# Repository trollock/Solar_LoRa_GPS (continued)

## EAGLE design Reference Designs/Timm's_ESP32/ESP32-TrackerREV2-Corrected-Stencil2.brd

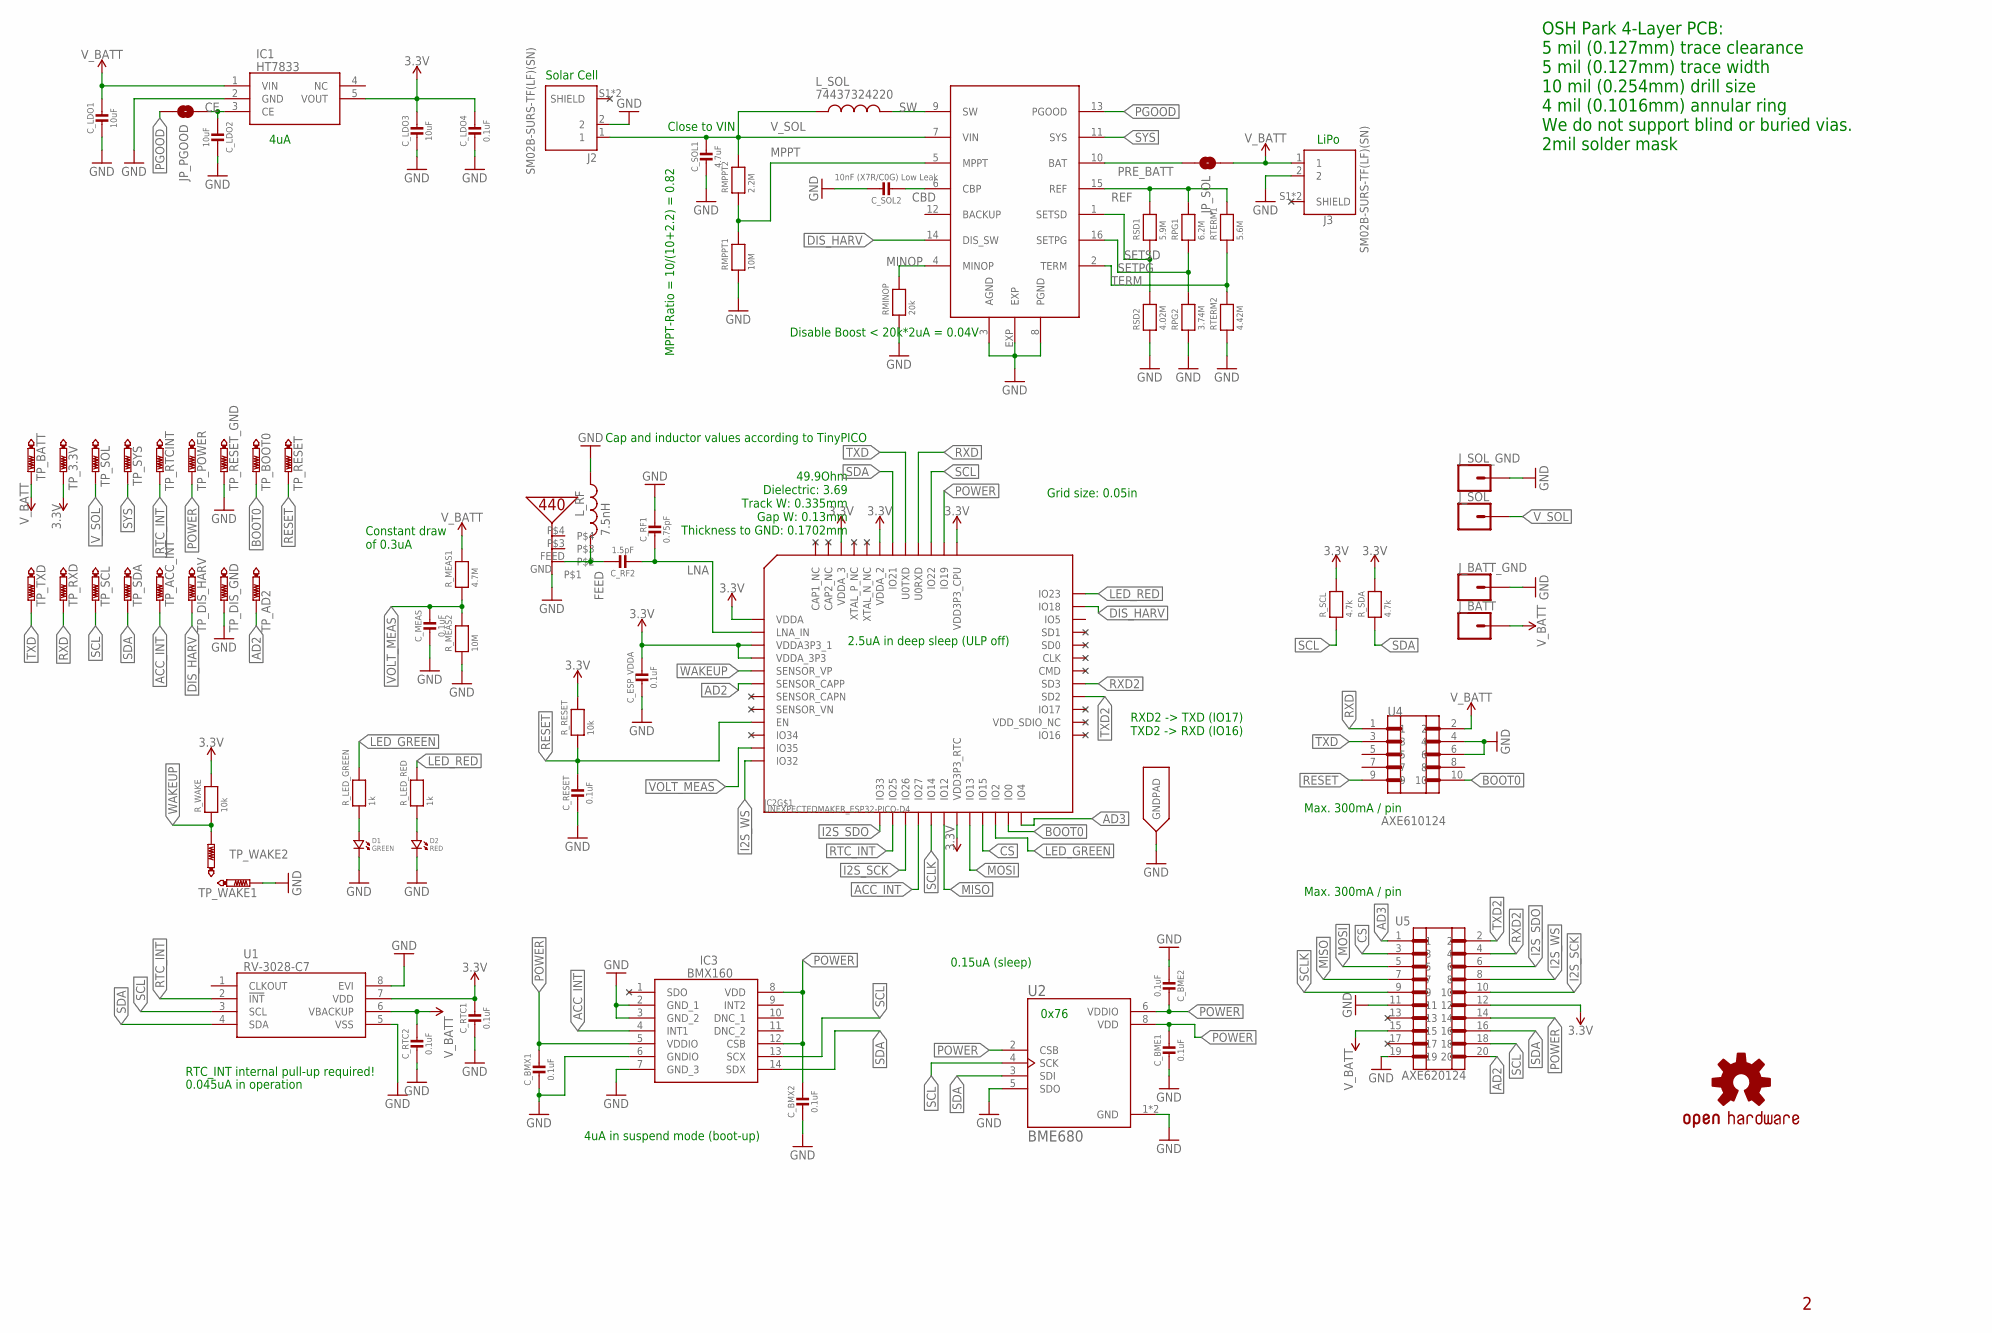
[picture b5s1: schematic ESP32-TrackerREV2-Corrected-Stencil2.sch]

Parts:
C_BME1, C_BME2: 0.1uF; MICROBUILDER__0402MP
C_BMX1, C_BMX2: 0.1uF; MICROBUILDER__0402MP
C_ESP_VDDA: 0.1uF; MICROBUILDER__0402MP
C_LDO1, C_LDO2, C_LDO3: 10uF; MICROBUILDER__0402MP
C_LDO4: 0.1uF; MICROBUILDER__0402MP
C_MEAS: 0.1uF; MICROBUILDER__0402MP
C_RESET: 0.1uF; MICROBUILDER__0402MP
C_RF1: 0.75pF; MICROBUILDER__0402MP
C_RF2: 1.5pF; MICROBUILDER__0402MP
C_RTC1, C_RTC2: 0.1uF; MICROBUILDER__0402MP
C_SOL1: 4.7uF; MICROBUILDER__0402MP
C_SOL2: 10nF (X7R/C0G) Low Leak; MICROBUILDER__0402MP
D1: GREEN; CMONR_STANDARDPARTS_0402.LED
D2: RED; CMONR_STANDARDPARTS_0402.LED
IC1: HT7833; SOT95P280X80-5N
IC2: UNEXPECTEDMAKER_ESP32-PICO-D4; UNEXPECTEDMAKER_PICO-D4-QFN48
IC3: BMX160; PQFN50P300X250X88-14N
J2, J3: SM02B-SURS-TF(LF)(SN); JST_SM02B-SURS-TF(LF)(SN)
JP_PGOOD: JUMPER-SMT_2_NO_NO-SILK; SMT-JUMPER_2_NO_NO-SILK
JP_SOL: JUMPER-SMT_2_NO_NO-SILK; SMT-JUMPER_2_NO_NO-SILK
J_BATT: CONN_01PTH_NO_SILK_SMALL; 1X01_SMALL
J_BATT_GND: CONN_01PTH_NO_SILK_SMALL; 1X01_SMALL
J_SOL: CONN_01PTH_NO_SILK_SMALL; 1X01_SMALL
J_SOL_GND: CONN_01PTH_NO_SILK_SMALL; 1X01_SMALL
LOGO1: OSHW-LOGOS; OSHW-LOGO-S
L_RF: 7.5nH; NORDIC_NRF_RESC0402_N
L_SOL: 74437324220; IND_74437324220
RMINOP: 20k; MICROBUILDER__0402MP
RMPPT1: 10M; MICROBUILDER__0402MP
RMPPT2: 2.2M; MICROBUILDER__0402MP
RPG1: 6.2M; MICROBUILDER__0402MP
RPG2: 3.74M; MICROBUILDER__0402MP
RSD1: 5.9M; MICROBUILDER__0402MP
RSD2: 4.02M; MICROBUILDER__0402MP
RTERM1: 5.6M; MICROBUILDER__0402MP
RTERM2: 4.42M; MICROBUILDER__0402MP
R_LED_GREEN: 1k; MICROBUILDER__0402MP
R_LED_RED: 1k; MICROBUILDER__0402MP
R_MEAS1: 4.7M; MICROBUILDER__0402MP
R_MEAS2: 10M; MICROBUILDER__0402MP
R_RESET: 10k; MICROBUILDER__0402MP
R_SCL: 4.7k; MICROBUILDER__0402MP
R_SDA: 4.7k; MICROBUILDER__0402MP
R_WAKE: 10k; MICROBUILDER__0402MP
TP_3.3V: PTR1TP06SQ; TP06SQ
TP_ACC_INT: PTR1TP06SQ; TP06SQ
TP_AD2: PTR1TP06SQ; TP06SQ
TP_BATT: PTR1TP06SQ; TP06SQ
TP_BOOT0: PTR1TP06SQ; TP06SQ
TP_DIS_GND: PTR1TP06SQ; TP06SQ
TP_DIS_HARV: PTR1TP06SQ; TP06SQ
TP_POWER: PTR1TP06SQ; TP06SQ
TP_RESET: PTR1TP06SQ; TP06SQ
TP_RESET_GND: PTR1TP06SQ; TP06SQ
TP_RTCINT: PTR1TP06SQ; TP06SQ
TP_RXD: PTR1TP06SQ; TP06SQ
TP_SCL: PTR1TP06SQ; TP06SQ
TP_SDA: PTR1TP06SQ; TP06SQ
TP_SOL: PTR1TP06SQ; TP06SQ
TP_SYS: PTR1TP06SQ; TP06SQ
TP_TXD: PTR1TP06SQ; TP06SQ
TP_WAKE1, TP_WAKE2: PTR1TP06SQ; TP06SQ
U1: RV-3028-C7; RV3028C7
U2: BME680; PSON80P300X300X100-8N
U3: UNEXPECTEDMAKER_PRO-OB-440
U4: AXE610124
U5: AXE620124
U6: ADP5090_LFCSP-16-3X3_ADP5090; ADP5090_LFCSP-16-3X3_LFCSP-16-3X3

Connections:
3.3V: C_ESP_VDDA.1, C_LDO3.1, C_LDO4.1, C_RTC1.1, IC1.5 (VOUT), IC2.1 (VDDA), IC2.3 (VDDA3P3_1), IC2.4 (VDDA_3P3), IC2.19 (VDD3P3_RTC), IC2.37 (VDD3P3_CPU), IC2.43 (VDDA_2), IC2.46 (VDDA_3), R_RESET.2, R_SCL.2, R_SDA.2, R_WAKE.2, TP_3.3V.TP, U1.7 (VDD), U5.12
ACC_INT: IC2.16 (IO27), IC3.4 (INT1), TP_ACC_INT.TP
AD2: IC2.6 (SENSOR_CAPP), TP_AD2.TP, U5.20
AD3: IC2.24 (IO4), U5.1
BOOT0: IC2.23 (IO0), TP_BOOT0.TP, U4.10
CBD: C_SOL2.2, U6.6 (CBP)
CE: C_LDO2.2, IC1.3 (CE), JP_PGOOD.2
CS: IC2.21 (IO15), U5.3
DIS_HARV: IC2.35 (IO18), TP_DIS_HARV.TP, U6.14 (DIS_SW)
FEED: C_RF2.1, L_RF.2, U3.FEED
GND: C_BME1.2, C_BME2.2, C_BMX1.2, C_BMX2.2, C_ESP_VDDA.2, C_LDO1.2, C_LDO2.1, C_LDO3.2, C_LDO4.2, C_MEAS.2, C_RESET.2, C_RF1.1, C_RTC1.2, C_RTC2.2, C_SOL1.2, C_SOL2.1, D1.P$2 (2), D2.P$2 (2), IC1.2 (GND), IC2.EXP (GNDPAD), IC3.2 (GND_1), IC3.3 (GND_2), IC3.6 (GNDIO), IC3.7 (GND_3), J2.2, J3.2, J_BATT_GND.P$1, J_SOL_GND.P$1, L_RF.1, RMINOP.1, RMPPT1.1, RPG2.1, RSD2.1, RTERM2.1, R_MEAS2.1, TP_DIS_GND.TP, TP_RESET_GND.TP, TP_WAKE1.TP, U1.5 (VSS), U1.8 (EVI), U2.1 (GND), U2.5 (SDO), U2.7 (GND), U3.GND, U4.4, U4.6, U5.11, U5.19, U6.3 (AGND), U6.8 (PGND), U6.EXP
I2S_SCK: IC2.15 (IO26), U5.10
I2S_SDO: IC2.13 (IO33), U5.6
I2S_WS: IC2.12 (IO32), U5.8
LED_GREEN: IC2.22 (IO2), R_LED_GREEN.2
LED_RED: IC2.36 (IO23), R_LED_RED.2
LNA: C_RF1.2, C_RF2.2, IC2.2 (LNA_IN)
MINOP: RMINOP.2, U6.4 (MINOP)
MISO: IC2.18 (IO12), U5.7
MOSI: IC2.20 (IO13), U5.5
MPPT: RMPPT1.2, RMPPT2.1, U6.5 (MPPT)
unnamed: D1.P$1 (1), R_LED_GREEN.1
unnamed: D2.P$1 (1), R_LED_RED.1
PGOOD: JP_PGOOD.1, U6.13 (PGOOD)
POWER: C_BME1.1, C_BME2.1, C_BMX1.1, C_BMX2.1, IC2.38 (IO19), IC3.5 (VDDIO), IC3.8 (VDD), IC3.12 (CSB), TP_POWER.TP, U2.2 (CSB), U2.6 (VDDIO), U2.8 (VDD), U5.14
PRE_BATT: JP_SOL.1, U6.10 (BAT)
REF: RPG1.2, RSD1.2, RTERM1.2, U6.15 (REF)
RESET: C_RESET.1, IC2.9 (EN), R_RESET.1, TP_RESET.TP, U4.9
RTC_INT: IC2.14 (IO25), TP_RTCINT.TP, U1.2 (!INT)
RXD: IC2.40 (U0RXD), TP_RXD.TP, U4.1
RXD2: IC2.29 (SD3), U5.4
SCL: IC2.39 (IO22), IC3.13 (SCX), R_SCL.1, TP_SCL.TP, U1.3 (SCL), U2.4 (SCK), U5.18
SCLK: IC2.17 (IO14), U5.9
SDA: IC2.42 (IO21), IC3.14 (SDX), R_SDA.1, TP_SDA.TP, U1.4 (SDA), U2.3 (SDI), U5.16
SENSOR_CAPN: IC2.7 (SENSOR_CAPN)
SETPG: RPG1.1, RPG2.2, U6.16 (SETPG)
SETSD: RSD1.1, RSD2.2, U6.1 (SETSD)
SW: L_SOL.2, U6.9 (SW)
SYS: TP_SYS.TP, U6.11 (SYS)
TERM: RTERM1.1, RTERM2.2, U6.2 (TERM)
TXD: IC2.41 (U0TXD), TP_TXD.TP, U4.3
TXD2: IC2.28 (SD2), U5.2
VOLT_MEAS: C_MEAS.1, IC2.11 (IO35), R_MEAS1.1, R_MEAS2.2
V_BATT: C_LDO1.1, C_RTC2.1, IC1.1 (VIN), J3.1, JP_SOL.2, J_BATT.P$1, R_MEAS1.2, TP_BATT.TP, U1.6 (VBACKUP), U4.2, U5.15
V_SOL: C_SOL1.1, J2.1, J_SOL.P$1, L_SOL.1, RMPPT2.2, TP_SOL.TP, U6.7 (VIN)
WAKEUP: IC2.5 (SENSOR_VP), R_WAKE.1, TP_WAKE2.TP

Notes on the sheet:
Cap and inductor values according to TinyPICO
Grid size: 0.05in
RXD2 -> TXD (IO17) TXD2 -> RXD (IO16)
RTC_INT internal pull-up required!
Constant draw of 0.3uA
Disable Boost < 20k*2uA = 0.04V
Close to VIN
Solar Cell
LiPo
4uA in suspend mode (boot-up)
0.045uA in operation
4uA
2.5uA in deep sleep (ULP off)
OSH Park 4-Layer PCB: 5 mil (0.127mm) trace clearance 5 mil (0.127mm) trace width 10 mil (0.254mm) drill size 4 mil (0.1016mm) annular ring We do not support blind or buried vias. 2mil solder mask
0x76
Max. 300mA / pin
MPPT-Ratio = 10/(10+2.2) = 0.82
49.9Ohm Dielectric: 3.69 Track W: 0.335mm Gap W: 0.13mm Thickness to GND: 0.1702mm
0.15uA (sleep)

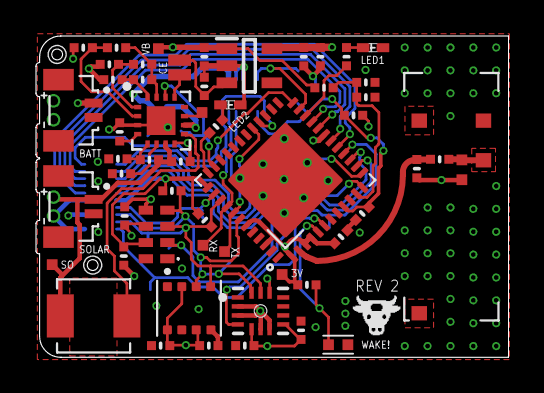
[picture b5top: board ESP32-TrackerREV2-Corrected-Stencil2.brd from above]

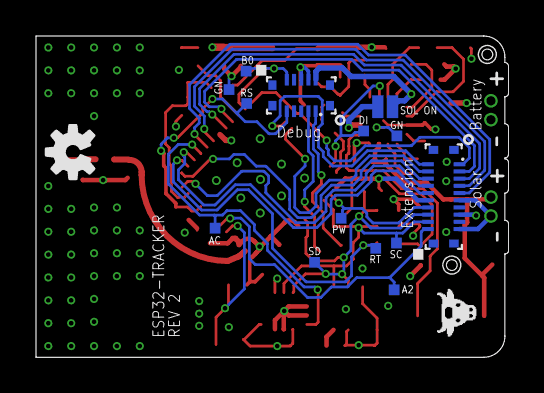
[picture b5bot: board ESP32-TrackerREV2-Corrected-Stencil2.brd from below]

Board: 4 copper layers, 26.2 x 17.9 mm, 75 parts (15 on the bottom side), 45 nets.
